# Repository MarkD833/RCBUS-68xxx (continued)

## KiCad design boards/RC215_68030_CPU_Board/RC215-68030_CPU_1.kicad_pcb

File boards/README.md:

# RCBUS-68000-Boards

These folders contain the KiCad (v8/v9/v10) design files for the various RCBus 68000 boards I'm currently testing.

## Series 1 boards

The series 1 boards are my first attempt at a 68000 based RCBus-80 system. Processor boards support autovectored interrupts only.

**NOTE:** The series 1 boards have been largly superseeded by the series 2 boards as my knowledge expanded and have generally been superseeded by the RC2xx series 2 boards.

| ID | Description | Notes |
| :---- | :---- | :---- |
| RC101 | 68000 processor card using the PLCC package variant of the 68000 | Use RC201 for vectored interrupt support |
| RC102 | 128K ROM & 1M RAM board | Use RC208 instead |
| RC103 | Dual MC68681 serial board - 4 serial ports | Use RC202 (2 serial ports only) for vectored interrupt support |
| RC104 | Dual MC68230 parallel interface / timer board | Use RC203 for vectored interrupt support (timer only) |
| RC105 | Dual MC68901 multifunction peripheral board | |
| RC106 | 68302 processor card using the PGA package | |
| RC107 | 1M ROM & 1M RAM board | Use RC208 instead |
| RC108 | 6 channel SPI master board - 3V3 and 5V ports | |
| RC109 | Serial / parallel / timer board | |
| RC110 | 68020 processor card using the PGA package | Use RC205 for vectored interrupt support |
| RC111 | SCC68692 DUART + MC68881 maths coprocessor | |

Note that the 68020 board is still very much at the prototype stage.

## Series 2 boards

The series 2 boards are based on my time spent with the series 1 boards and the hope is that the processor boards will feature a mixture of vectored and autovectored interrupts.

| ID | Description | Notes |
| :---- | :---- | :---- |
| RC200 | RCBus-80 Developers Backplane | |
| RC201 | 68000 PLCC processor board | Supports vectored interrupts |
| RC202 | SCC68692 DUART board | Bit banged SPI & I2C ports |
| RC203 | Dual MC68230 parallel interface / timer board | |
| RC204 | 1M ROM & 3M RAM board | Untested but likely replaced with RC209 shortly |
| RC205 | 68020 PGA processor board | Supports vectored interrupts |
| RC206 | 68008 PLCC processor board | |
| RC207 | 1M ROM & 1M RAM board - manual BOOT ROM switching | Abandoned - use RC208 instead |
| RC208 | 1M ROM & 1M RAM board - automatic BOOT ROM switching | |
| RC209 | 1M ROM & 3M RAM board - automatic BOOT ROM switching | |
| RC215 | 68EC030 PGA processor board | Supports vectored interrupts |
| RC216 | SCC68692 DUART + MC68882 Maths coprocessor | Bit banged I2C port |

Several of the series 2 boards are now working and I've put details in their respectove folders whilst others are still very much at the prototype stage.

## Notes
Make sure to look at the readme files in each board folder as they will detail any errors and corrections I've noticed so far as well as any thoughts on future enhancements etc.

A minimal series 2 system using a 68000, 68010, 68020 or 68EC030 processor requires an RC208 ROM/RAM board and a series 2 serial I/O board.

A minimal 68302 system would comprise of a 68302 CPU board and a ROM/RAM board.

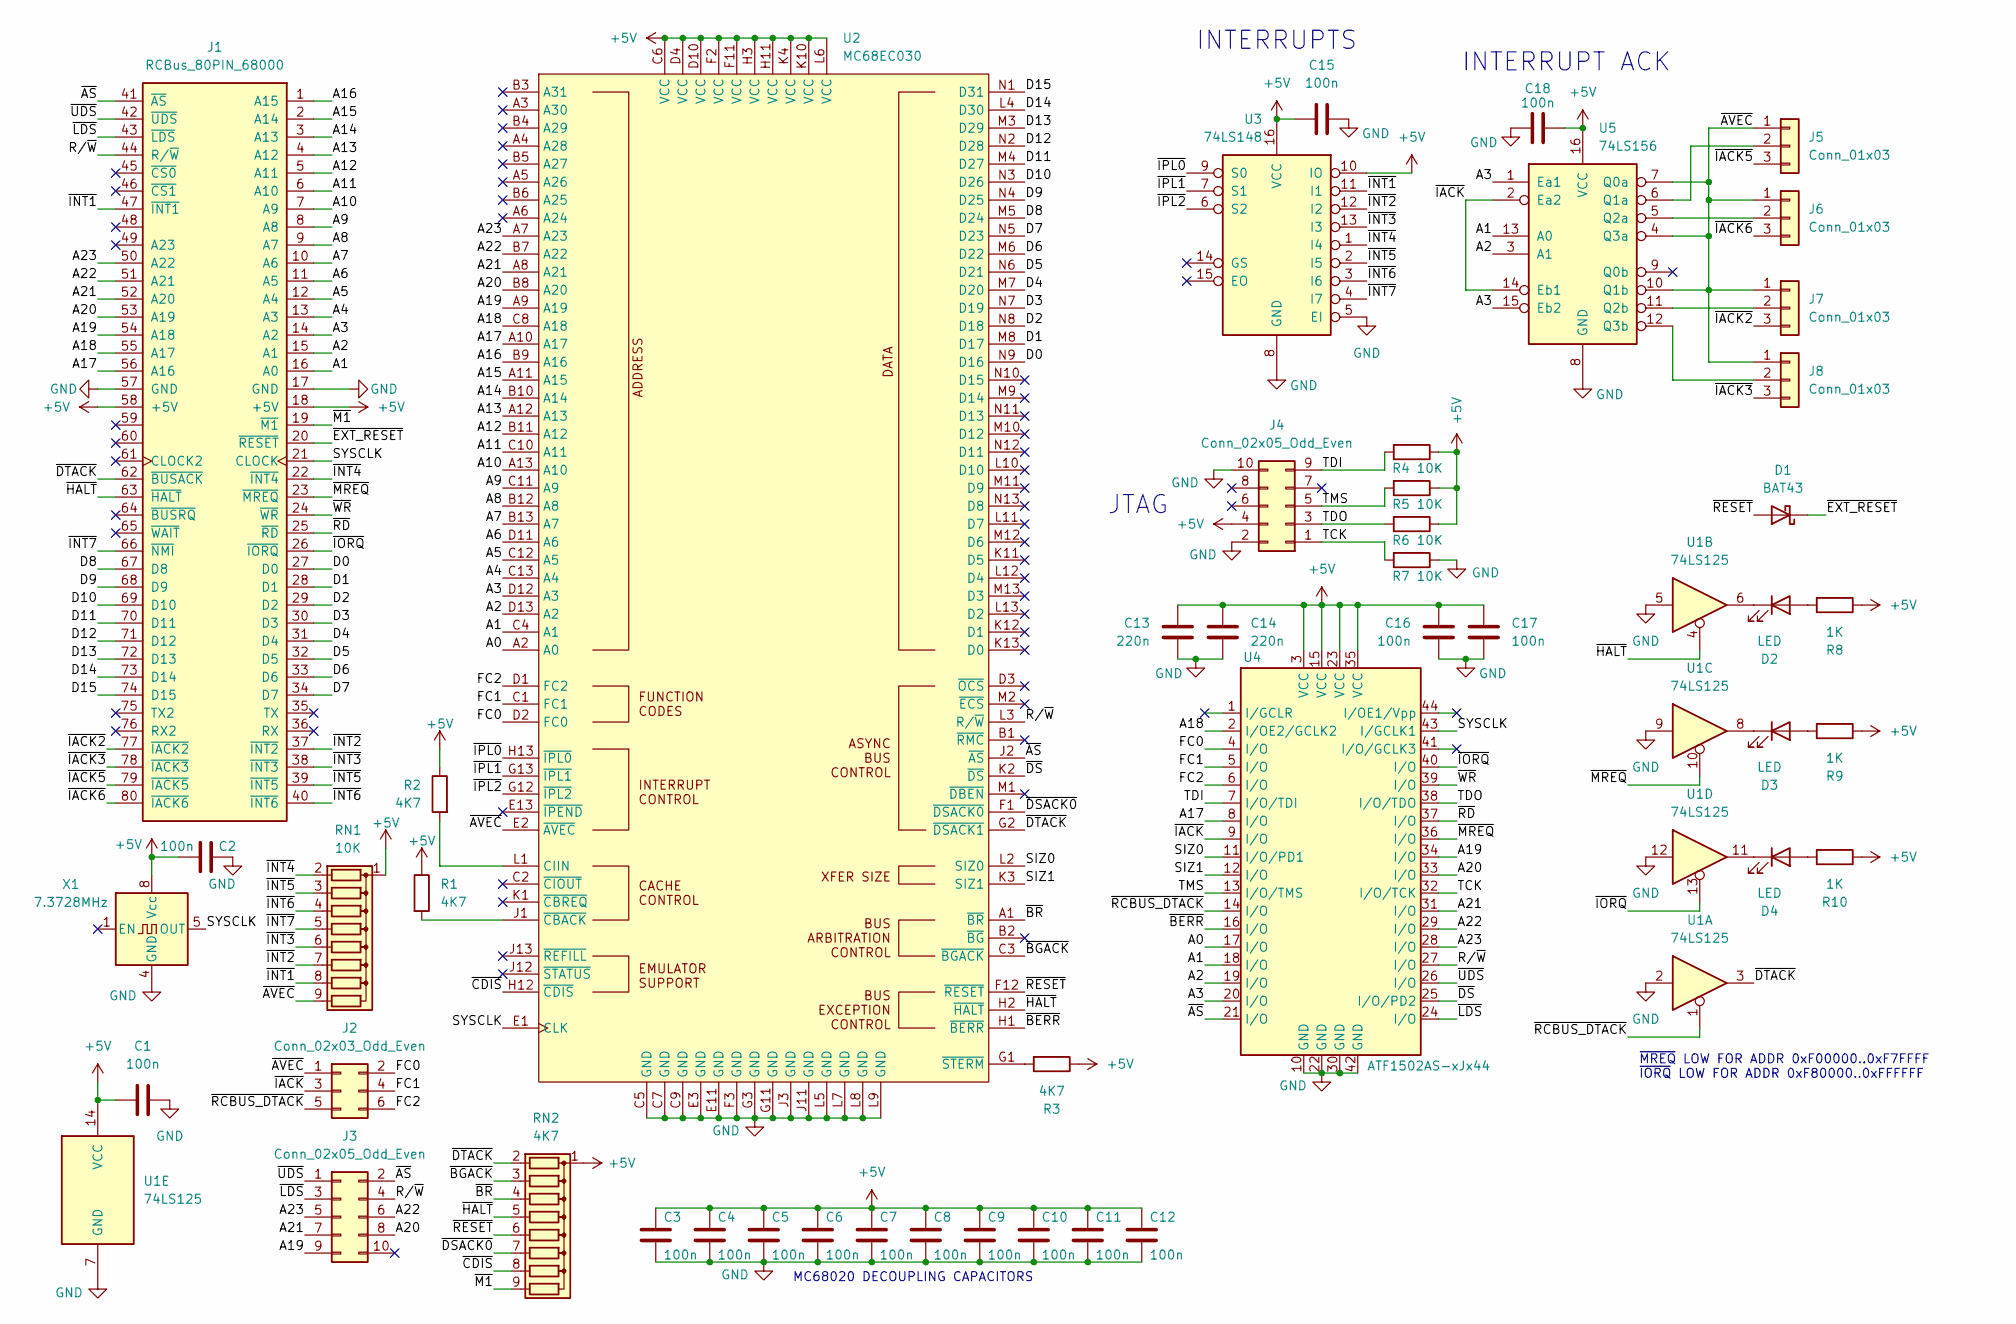
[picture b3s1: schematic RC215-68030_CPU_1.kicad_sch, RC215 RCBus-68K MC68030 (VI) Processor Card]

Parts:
C1, C2, C3, C4, C5, C6, C7, C8, C9, C10, C11, C12, C15, C16, C17, C18: 100n; C_0805_2012Metric_Pad1.18x1.45mm_HandSolder
C13, C14: 220n; C_0805_2012Metric_Pad1.18x1.45mm_HandSolder
D1: BAT43; D_DO-35_SOD27_P7.62mm_Horizontal
D2, D3, D4: LED; KingBright_WP934_1_LED
J1: RCBus_80PIN_68000; RCBus_80p_Medium
J2: Conn_02x03_Odd_Even; PinHeader_2x03_P2.54mm_Vertical
J3, J4: Conn_02x05_Odd_Even; PinHeader_2x05_P2.54mm_Vertical
J5, J6, J7, J8: Conn_01x03; PinHeader_1x03_P2.54mm_Vertical
R1, R2, R3: 4K7; R_0805_2012Metric_Pad1.20x1.40mm_HandSolder
R4, R5, R6, R7: 10K; R_0805_2012Metric_Pad1.20x1.40mm_HandSolder
R8, R9, R10: 1K; R_0805_2012Metric_Pad1.20x1.40mm_HandSolder
RN1: 10K; R_Array_SIP9
RN2: 4K7; R_Array_SIP9
U1: 74LS125; DIP-14_W7.62mm
U2: MC68EC030; PGA124
U3: 74LS148; DIP-16_W7.62mm
U4: ATF1502AS-xJx44; PLCC-44_THT-Socket
U5: 74LS156; DIP-16_W7.62mm
X1: 7.3728MHz; Oscillator_DIP-8

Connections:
+5V: C1.1, C2.2, C3.2, C4.2, C5.2, C6.2, C7.2, C8.2, C9.2, C10.2, C11.2, C12.2, C13.2, C14.2, C15.1, C16.1, C17.2, C18.1, J1.18 (+5V), J1.58 (+5V), J4.4, R1.1, R2.1, R3.1, R4.1, R5.1, R6.1, R8.1, R9.1, R10.1, RN1.1 (common), RN2.1 (common), U1.14 (VCC), U2.C6 (VCC), U2.D4 (VCC), U2.D10 (VCC), U2.F2 (VCC), U2.F11 (VCC), U2.H3 (VCC), U2.H11 (VCC), U2.K4 (VCC), U2.K10 (VCC), U2.L6 (VCC), U3.10 (IO), U3.16 (VCC), U4.3 (VCC), U4.15 (VCC), U4.23 (VCC), U4.35 (VCC), U5.16 (VCC), X1.8 (Vcc)
/A0: U2.A2 (A0), U4.17 (I/O)
/A1: J1.16 (A0), U2.C4 (A1), U4.18 (I/O), U5.13 (A0)
/A2: J1.15 (A1), U2.D13 (A2), U4.19 (I/O), U5.3 (A1)
/A3: J1.14 (A2), U2.D12 (A3), U4.20 (I/O), U5.1 (Ea1), U5.15 (Eb2)
/A4: J1.13 (A3), U2.C13 (A4)
/A5: J1.12 (A4), U2.C12 (A5)
/A6: J1.11 (A5), U2.D11 (A6)
/A7: J1.10 (A6), U2.B13 (A7)
/A8: J1.9 (A7), U2.B12 (A8)
/A9: J1.8 (A8), U2.C11 (A9)
/A10: J1.7 (A9), U2.A13 (A10)
/A11: J1.6 (A10), U2.C10 (A11)
/A12: J1.5 (A11), U2.B11 (A12)
/A13: J1.4 (A12), U2.A12 (A13)
/A14: J1.3 (A13), U2.B10 (A14)
/A15: J1.2 (A14), U2.A11 (A15)
/A16: J1.1 (A15), U2.B9 (A16)
/A17: J1.56 (A16), U2.A10 (A17), U4.8 (I/O)
/A18: J1.55 (A17), U2.C8 (A18), U4.2 (I/OE2/GCLK2)
/A19: J1.54 (A18), J3.9, U2.A9 (A19), U4.34 (I/O)
/A20: J1.53 (A19), J3.8, U2.B8 (A20), U4.33 (I/O)
/A21: J1.52 (A20), J3.7, U2.A8 (A21), U4.31 (I/O)
/A22: J1.51 (A21), J3.6, U2.B7 (A22), U4.29 (I/O)
/A23: J1.50 (A22), J3.5, U2.A7 (A23), U4.28 (I/O)
/D0: J1.27 (D0), U2.N9 (D16)
/D1: J1.28 (D1), U2.M8 (D17)
/D2: J1.29 (D2), U2.N8 (D18)
/D3: J1.30 (D3), U2.N7 (D19)
/D4: J1.31 (D4), U2.M7 (D20)
/D5: J1.32 (D5), U2.N6 (D21)
/D6: J1.33 (D6), U2.M6 (D22)
/D7: J1.34 (D7), U2.N5 (D23)
/D8: J1.67 (D8), U2.M5 (D24)
/D9: J1.68 (D9), U2.N4 (D25)
/D10: J1.69 (D10), U2.N3 (D26)
/D11: J1.70 (D11), U2.M4 (D27)
/D12: J1.71 (D12), U2.N2 (D28)
/D13: J1.72 (D13), U2.M3 (D29)
/D14: J1.73 (D14), U2.L4 (D30)
/D15: J1.74 (D15), U2.N1 (D31)
/FC0: J2.2, U2.D2 (FC0), U4.4 (I/O)
/FC1: J2.4, U2.C1 (FC1), U4.5 (I/O)
/FC2: J2.6, U2.D1 (FC2), U4.6 (I/O)
/R/~W: J1.44 (R/~W), J3.4, U2.L3 (R/~W), U4.27 (I/O)
/SIZ0: U2.L2 (SIZ0), U4.11 (I/O/PD1)
/SIZ1: U2.K3 (SIZ1), U4.12 (I/O)
/SYSCLK: J1.21 (CLOCK), U2.E1 (CLK), U4.43 (I/GCLK1), X1.5 (OUT)
/TCK: J4.1, R7.2, U4.32 (I/O/TCK)
/TDI: J4.9, R4.2, U4.7 (I/O/TDI)
/TDO: J4.3, R6.2, U4.38 (I/O/TDO)
/TMS: J4.5, R5.2, U4.13 (I/O/TMS)
/~AS: J1.41 (~AS), J3.2, U2.J2 (~AS), U4.21 (I/O)
/~AVEC: J2.1, J5.1, J6.1, J7.1, J8.1, RN1.9 (R8), U2.E2 (~AVEC), U5.4 (Q3a), U5.7 (Q0a), U5.10 (Q1b)
/~BERR: U2.H1 (~BERR), U4.16 (I/O)
/~BGACK: RN2.3 (R2), U2.C3 (~BGACK)
/~BR: RN2.4 (R3), U2.A1 (~BR)
/~CDIS: RN2.8 (R7), U2.H12 (~CDIS)
/~DSACK0: RN2.7 (R6), U2.F1 (~DSACK0)
/~DS: U2.K2 (~DS), U4.25 (I/O/PD2)
/~DTACK: J1.62 (~BUSACK), RN2.2 (R1), U1.3, U2.G2 (~DSACK1)
/~EXT_RESET: D1.1 (K), J1.20 (~RESET)
/~HALT: J1.63 (~HALT), RN2.5 (R4), U1.4, U2.H2 (~HALT)
/~IACK2: J1.77 (~IACK2), J7.3
/~IACK3: J1.78 (~IACK3), J8.3
/~IACK5: J1.79 (~IACK5), J5.3
/~IACK6: J1.80 (~IACK6), J6.3
/~IACK: J2.3, U4.9 (I/O), U5.2 (Ea2), U5.14 (Eb1)
/~INT1: J1.47 (~INT1), RN1.8 (R7), U3.11 (I1)
/~INT2: J1.37 (~INT2), RN1.7 (R6), U3.12 (I2)
/~INT3: J1.38 (~INT3), RN1.6 (R5), U3.13 (I3)
/~INT4: J1.22 (~INT4), RN1.2 (R1), U3.1 (I4)
/~INT5: J1.39 (~INT5), RN1.3 (R2), U3.2 (I5)
/~INT6: J1.40 (~INT6), RN1.4 (R3), U3.3 (I6)
/~INT7: J1.66 (~NMI), RN1.5 (R4), U3.4 (I7)
/~IORQ: J1.26 (~IORQ), U1.13, U4.40 (I/O)
/~IPL0: U2.H13 (~IPL0), U3.9 (S0)
/~IPL1: U2.G13 (~IPL1), U3.7 (S1)
/~IPL2: U2.G12 (~IPL2), U3.6 (S2)
/~LDS: J1.43 (~LDS), J3.3, U4.24 (I/O)
/~M1: J1.19 (~M1), RN2.9 (R8)
/~MREQ: J1.23 (~MREQ), U1.10, U4.36 (I/O)
/~RCBUS_DTACK: J2.5, U1.1, U4.14 (I/O)
/~RD: J1.25 (~RD), U4.37 (I/O)
/~RESET: D1.2 (A), RN2.6 (R5), U2.F12 (~RESET)
/~UDS: J1.42 (~UDS), J3.1, U4.26 (I/O)
/~WR: J1.24 (~WR), U4.39 (I/O)
GND: C1.2, C2.1, C3.1, C4.1, C5.1, C6.1, C7.1, C8.1, C9.1, C10.1, C11.1, C12.1, C13.1, C14.1, C15.2, C16.2, C17.1, C18.2, J1.17 (GND), J1.57 (GND), J4.2, J4.10, R7.1, U1.2, U1.5, U1.7 (GND), U1.9, U1.12, U2.C5 (GND), U2.C7 (GND), U2.C9 (GND), U2.E3 (GND), U2.E11 (GND), U2.F3 (GND), U2.G3 (GND), U2.G11 (GND), U2.J3 (GND), U2.J11 (GND), U2.L5 (GND), U2.L7 (GND), U2.L8 (GND), U2.L9 (GND), U3.5 (EI), U3.8 (GND), U4.10 (GND), U4.22 (GND), U4.30 (GND), U4.42 (GND), U5.8 (GND), X1.4 (GND)
unnamed: D2.2 (A), R8.2
unnamed: D2.1 (K), U1.6
unnamed: D3.2 (A), R9.2
unnamed: D3.1 (K), U1.8
unnamed: D4.2 (A), R10.2
unnamed: D4.1 (K), U1.11
unnamed: J5.2, U5.6 (Q1a)
unnamed: J6.2, U5.5 (Q2a)
unnamed: J7.2, U5.11 (Q2b)
unnamed: J8.2, U5.12 (Q3b)
unnamed: R2.2, U2.L1 (CIIN)
unnamed: R1.2, U2.J1 (~CBACK)
unnamed: R3.2, U2.G1 (~STERM)

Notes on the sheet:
MC68020 DECOUPLING CAPACITORS
INTERRUPTS
~{MREQ} LOW FOR ADDR 0xF00000..0xF7FFFF ~{IORQ} LOW FOR ADDR 0xF80000..0xFFFFFF
INTERRUPT ACK
JTAG

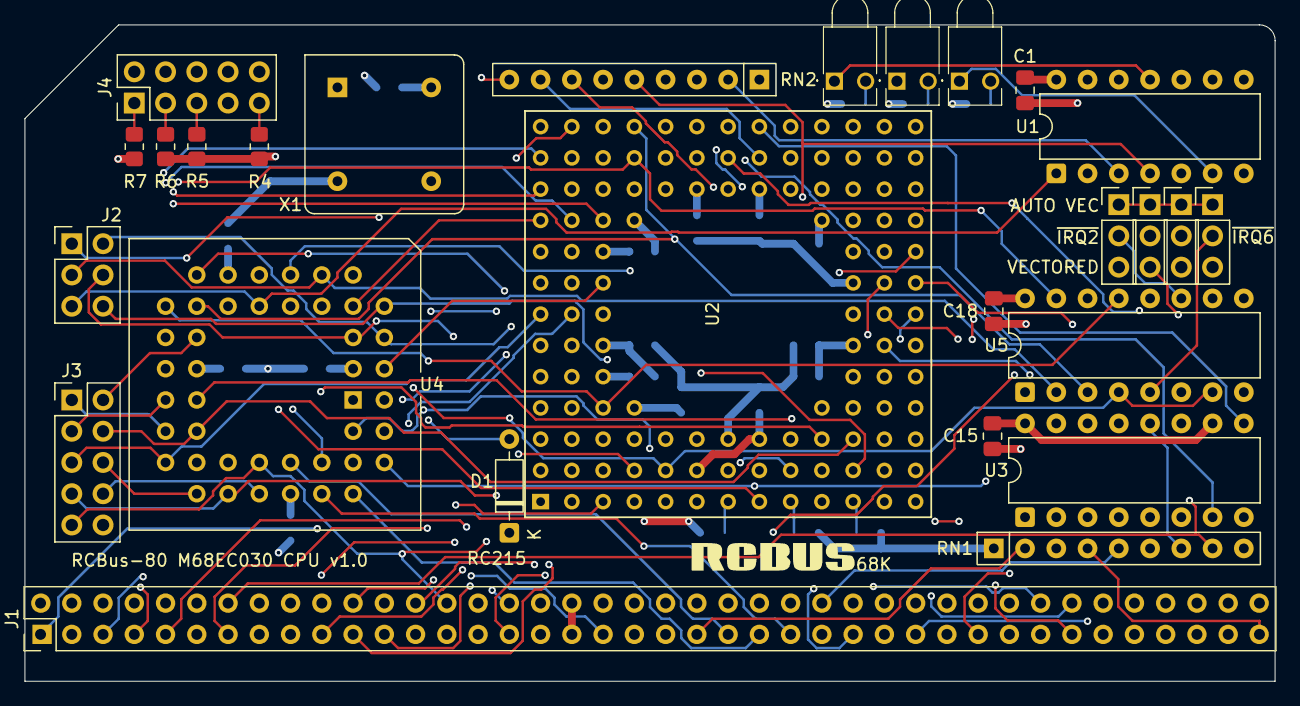
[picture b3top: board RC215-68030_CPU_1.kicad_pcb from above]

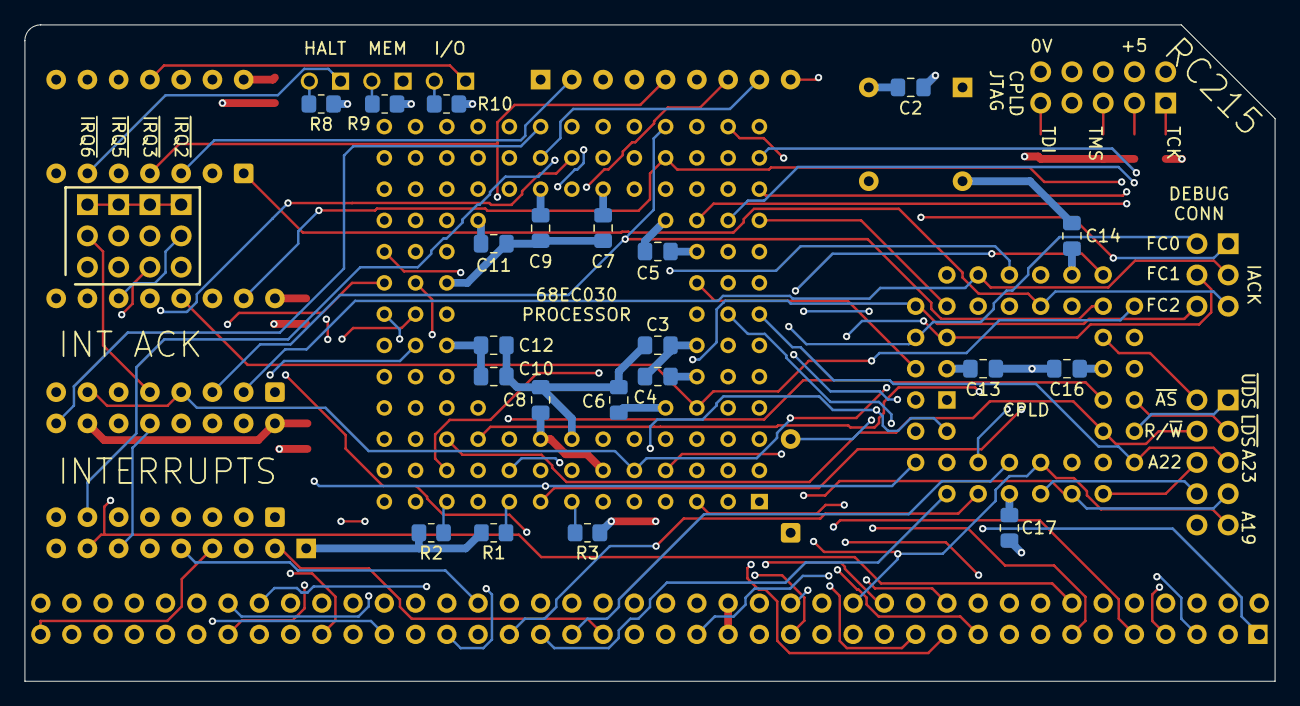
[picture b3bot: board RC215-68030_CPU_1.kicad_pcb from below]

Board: 4 copper layers, 101.6 x 53.3 mm, 48 parts (21 on the bottom side), 101 nets.

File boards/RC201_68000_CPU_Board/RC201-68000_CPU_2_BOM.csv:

"Reference","Value","Footprint","Qty","Description"
"C1,C2,C3,C5,C6,C7,C8,C9,C10,C11,C12","100n","Capacitor_THT:C_Disc_D5.0mm_W2.5mm_P2.50mm","11","Unpolarized ceramic capacitor"
"D1,D2,D5","BAT43","Diode_THT:D_DO-35_SOD27_P7.62mm_Horizontal","3","30V 0.2A Small Signal Schottky Diode, DO-35"
"D3,D4","LED","LED_THT:LED_D3.0mm","2","Light emitting diode"
"J1","Conn_02x04_Odd_Even","Connector_PinHeader_2.54mm:PinHeader_2x04_P2.54mm_Vertical","1","Generic connector, double row, 02x04"
"J2","RCBus_80PIN_68000","MyLibrary2023:RCBus_80p_Medium","1","Generic connector, double row, 02x40, right angle"
"J3,J5,J6,J7","Conn_01x03","Connector_PinHeader_2.54mm:PinHeader_1x03_P2.54mm_Vertical","4","Generic connector, single row, 01x03, script generated (kicad-library-utils/schlib/autogen/connector/)"
"J4","Conn_01x02","Connector_PinHeader_2.54mm:PinHeader_1x02_P2.54mm_Vertical","1","Generic connector, single row, 01x02"
"R1,R2","1K","Resistor_THT:R_Axial_DIN0207_L6.3mm_D2.5mm_P7.62mm_Horizontal","2","Resistor"
"RN1","4K7","Resistor_THT:R_Array_SIP9","1","8 resistor network, star topology, bussed resistors, small symbol"
"RN2","10K","Resistor_THT:R_Array_SIP9","1","8 resistor network, star topology, bussed resistors, small symbol"
"U1","","Package_LCC:PLCC-68_THT-Socket","1",""
"U2","74LS04","MyLibrary2023:DIP-14_W7.62mm","1","Hex Inverter"
"U3","74LS148","MyLibrary2023:DIP-16_W7.62mm","1","8 line to 3 line priority encoder"
"U4","74LS20","MyLibrary2023:DIP-14_W7.62mm","1","Dual 4-input NAND"
"U5","74LS139","MyLibrary2023:DIP-16_W7.62mm","1","Dual Decoder 1 of 4, Active low outputs"
"U6,U8","74LS175","MyLibrary2023:DIP-16_W7.62mm","2","4-bit D Flip-Flop, reset"
"U7","74LS156","MyLibrary2023:DIP-16_W7.62mm","1","Dual 2 to 4 lines Decoder/Demultiplexer, Open Collector"
"U9","74LS00","MyLibrary2023:DIP-14_W7.62mm","1","quad 2-input NAND gate"
"X1","7.3728MHz","Oscillator:Oscillator_DIP-8","1","Crystal Clock Oscillator, DIP8-style metal package"

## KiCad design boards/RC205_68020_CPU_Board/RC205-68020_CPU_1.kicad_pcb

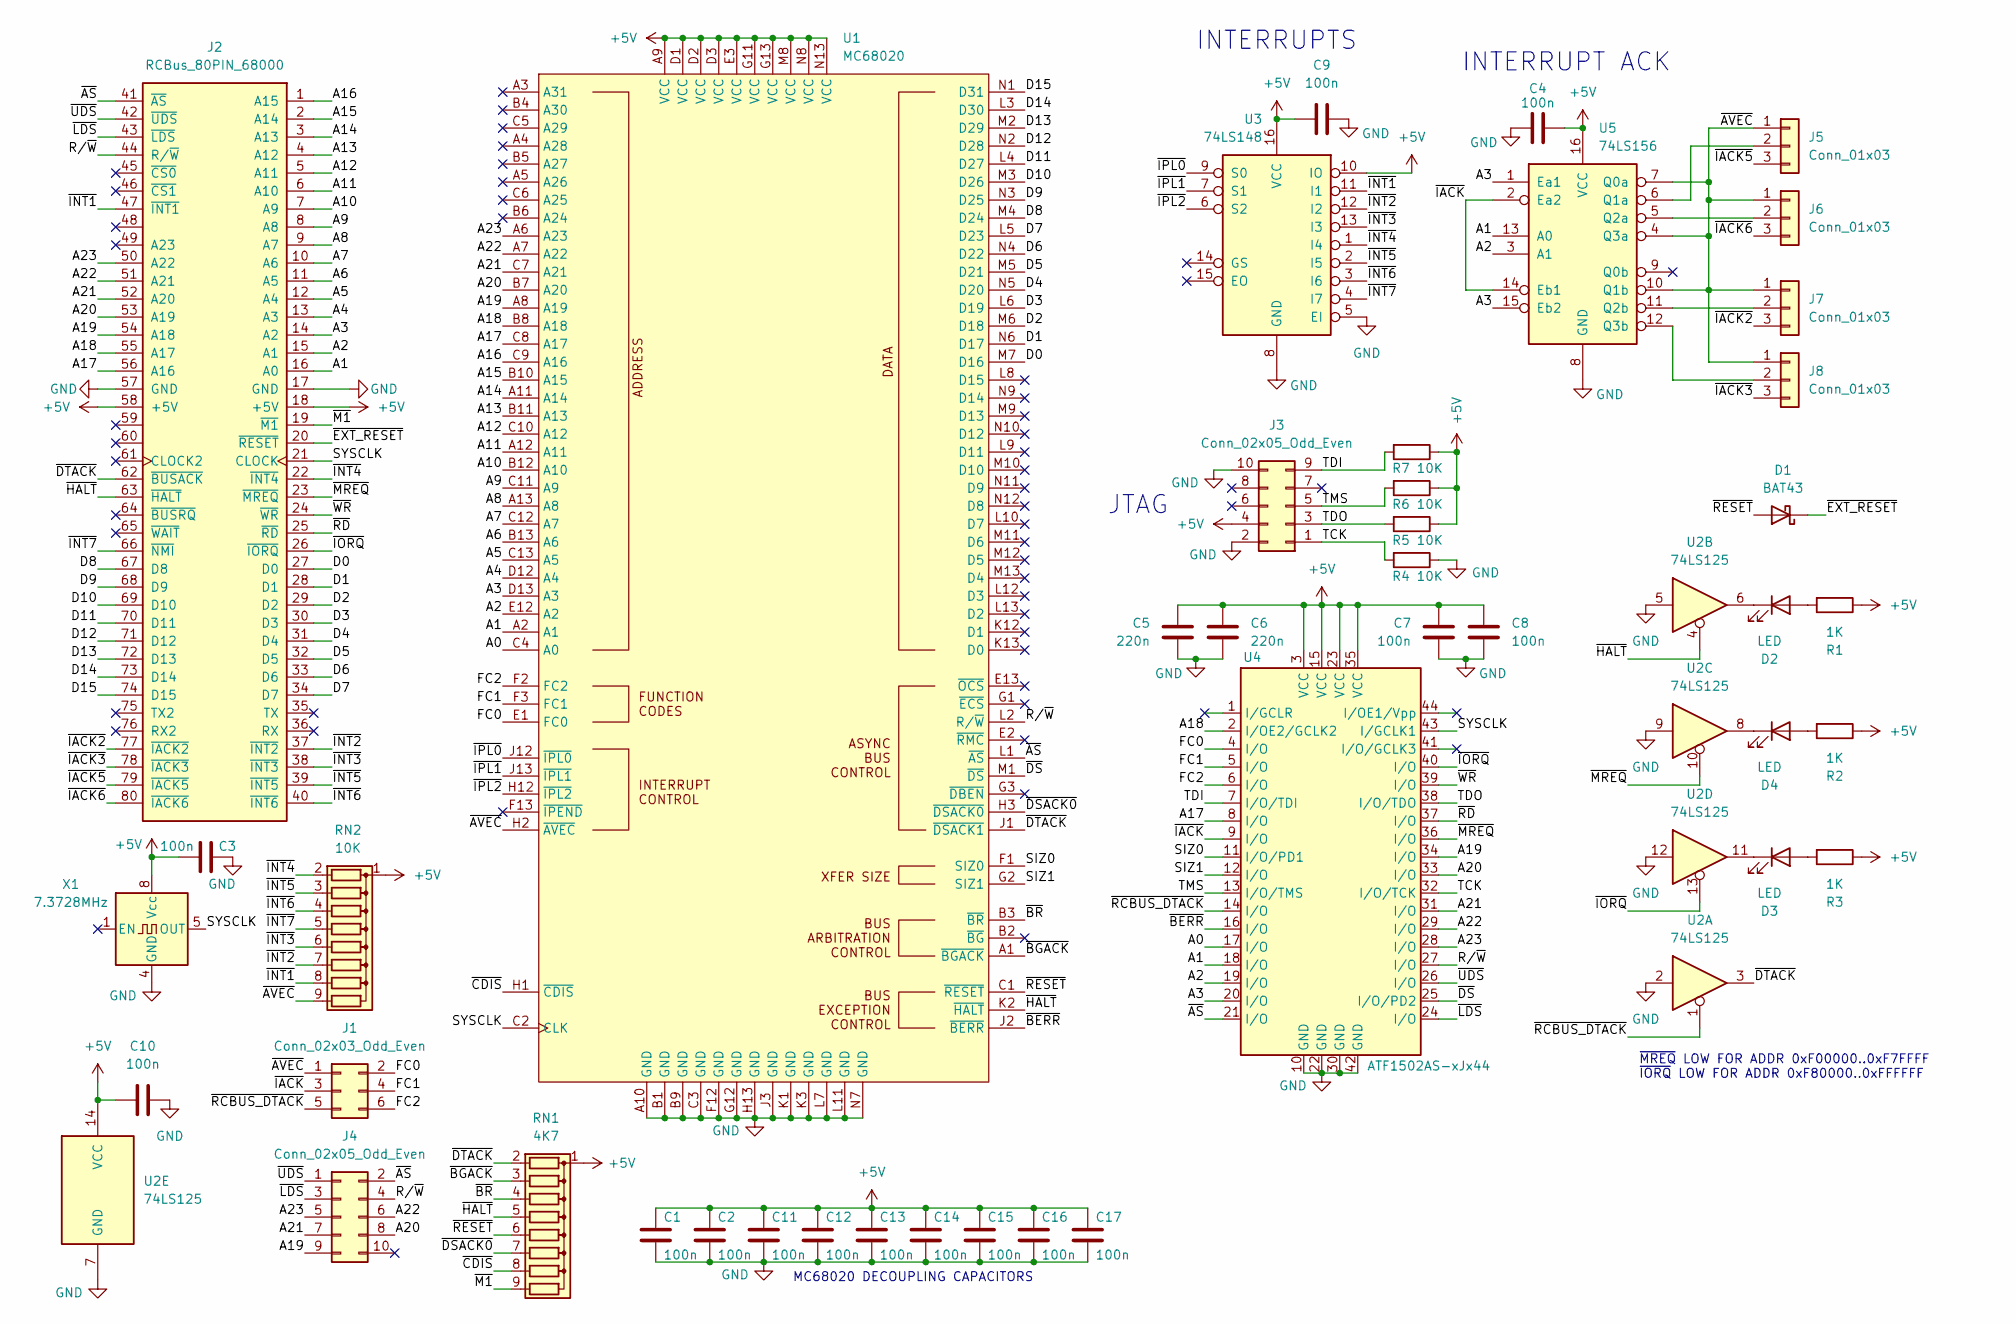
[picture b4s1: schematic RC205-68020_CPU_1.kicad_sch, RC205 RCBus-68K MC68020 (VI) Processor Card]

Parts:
C1, C2, C3, C4, C7, C8, C9, C10, C11, C12, C13, C14, C15, C16, C17: 100n; C_0805_2012Metric_Pad1.18x1.45mm_HandSolder
C5, C6: 220n; C_0805_2012Metric_Pad1.18x1.45mm_HandSolder
D1: BAT43; D_DO-35_SOD27_P7.62mm_Horizontal
D2, D3, D4: LED; LED_D3.0mm
J1: Conn_02x03_Odd_Even; PinHeader_2x03_P2.54mm_Vertical
J2: RCBus_80PIN_68000; RCBus_80p_Medium
J3, J4: Conn_02x05_Odd_Even; PinHeader_2x05_P2.54mm_Vertical
J5, J6, J7, J8: Conn_01x03; PinHeader_1x03_P2.54mm_Vertical
R1, R2, R3: 1K; R_0805_2012Metric_Pad1.20x1.40mm_HandSolder
R4, R5, R6, R7: 10K; R_0805_2012Metric_Pad1.20x1.40mm_HandSolder
RN1: 4K7; R_Array_SIP9
RN2: 10K; R_Array_SIP9
U1: MC68020; PGA114
U2: 74LS125; DIP-14_W7.62mm
U3: 74LS148; DIP-16_W7.62mm
U4: ATF1502AS-xJx44; PLCC-44_THT-Socket
U5: 74LS156; DIP-16_W7.62mm
X1: 7.3728MHz; Oscillator_DIP-8

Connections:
+5V: C1.2, C2.2, C3.2, C4.1, C5.2, C6.2, C7.1, C8.2, C9.1, C10.1, C11.2, C12.2, C13.2, C14.2, C15.2, C16.2, C17.2, J2.18 (+5V), J2.58 (+5V), J3.4, R1.1, R2.1, R3.1, R5.1, R6.1, R7.1, RN1.1 (common), RN2.1 (common), U1.A9 (VCC), U1.D1 (VCC), U1.D2 (VCC), U1.D3 (VCC), U1.E3 (VCC), U1.G11 (VCC), U1.G13 (VCC), U1.M8 (VCC), U1.N8 (VCC), U1.N13 (VCC), U2.14 (VCC), U3.10 (IO), U3.16 (VCC), U4.3 (VCC), U4.15 (VCC), U4.23 (VCC), U4.35 (VCC), U5.16 (VCC), X1.8 (Vcc)
/A0: U1.C4 (A0), U4.17 (I/O)
/A1: J2.16 (A0), U1.A2 (A1), U4.18 (I/O), U5.13 (A0)
/A2: J2.15 (A1), U1.E12 (A2), U4.19 (I/O), U5.3 (A1)
/A3: J2.14 (A2), U1.D13 (A3), U4.20 (I/O), U5.1 (Ea1), U5.15 (Eb2)
/A4: J2.13 (A3), U1.D12 (A4)
/A5: J2.12 (A4), U1.C13 (A5)
/A6: J2.11 (A5), U1.B13 (A6)
/A7: J2.10 (A6), U1.C12 (A7)
/A8: J2.9 (A7), U1.A13 (A8)
/A9: J2.8 (A8), U1.C11 (A9)
/A10: J2.7 (A9), U1.B12 (A10)
/A11: J2.6 (A10), U1.A12 (A11)
/A12: J2.5 (A11), U1.C10 (A12)
/A13: J2.4 (A12), U1.B11 (A13)
/A14: J2.3 (A13), U1.A11 (A14)
/A15: J2.2 (A14), U1.B10 (A15)
/A16: J2.1 (A15), U1.C9 (A16)
/A17: J2.56 (A16), U1.C8 (A17), U4.8 (I/O)
/A18: J2.55 (A17), U1.B8 (A18), U4.2 (I/OE2/GCLK2)
/A19: J2.54 (A18), J4.9, U1.A8 (A19), U4.34 (I/O)
/A20: J2.53 (A19), J4.8, U1.B7 (A20), U4.33 (I/O)
/A21: J2.52 (A20), J4.7, U1.C7 (A21), U4.31 (I/O)
/A22: J2.51 (A21), J4.6, U1.A7 (A22), U4.29 (I/O)
/A23: J2.50 (A22), J4.5, U1.A6 (A23), U4.28 (I/O)
/D0: J2.27 (D0), U1.M7 (D16)
/D1: J2.28 (D1), U1.N6 (D17)
/D2: J2.29 (D2), U1.M6 (D18)
/D3: J2.30 (D3), U1.L6 (D19)
/D4: J2.31 (D4), U1.N5 (D20)
/D5: J2.32 (D5), U1.M5 (D21)
/D6: J2.33 (D6), U1.N4 (D22)
/D7: J2.34 (D7), U1.L5 (D23)
/D8: J2.67 (D8), U1.M4 (D24)
/D9: J2.68 (D9), U1.N3 (D25)
/D10: J2.69 (D10), U1.M3 (D26)
/D11: J2.70 (D11), U1.L4 (D27)
/D12: J2.71 (D12), U1.N2 (D28)
/D13: J2.72 (D13), U1.M2 (D29)
/D14: J2.73 (D14), U1.L3 (D30)
/D15: J2.74 (D15), U1.N1 (D31)
/FC0: J1.2, U1.E1 (FC0), U4.4 (I/O)
/FC1: J1.4, U1.F3 (FC1), U4.5 (I/O)
/FC2: J1.6, U1.F2 (FC2), U4.6 (I/O)
/R/~W: J2.44 (R/~W), J4.4, U1.L2 (R/~W), U4.27 (I/O)
/SIZ0: U1.F1 (SIZ0), U4.11 (I/O/PD1)
/SIZ1: U1.G2 (SIZ1), U4.12 (I/O)
/SYSCLK: J2.21 (CLOCK), U1.C2 (CLK), U4.43 (I/GCLK1), X1.5 (OUT)
/TCK: J3.1, R4.2, U4.32 (I/O/TCK)
/TDI: J3.9, R7.2, U4.7 (I/O/TDI)
/TDO: J3.3, R5.2, U4.38 (I/O/TDO)
/TMS: J3.5, R6.2, U4.13 (I/O/TMS)
/~AS: J2.41 (~AS), J4.2, U1.L1 (~AS), U4.21 (I/O)
/~AVEC: J1.1, J5.1, J6.1, J7.1, J8.1, RN2.9 (R8), U1.H2 (~AVEC), U5.4 (Q3a), U5.7 (Q0a), U5.10 (Q1b)
/~BERR: U1.J2 (~BERR), U4.16 (I/O)
/~BGACK: RN1.3 (R2), U1.A1 (~BGACK)
/~BR: RN1.4 (R3), U1.B3 (~BR)
/~CDIS: RN1.8 (R7), U1.H1 (~CDIS)
/~DSACK0: RN1.7 (R6), U1.H3 (~DSACK0)
/~DS: U1.M1 (~DS), U4.25 (I/O/PD2)
/~DTACK: J2.62 (~BUSACK), RN1.2 (R1), U1.J1 (~DSACK1), U2.3
/~EXT_RESET: D1.1 (K), J2.20 (~RESET)
/~HALT: J2.63 (~HALT), RN1.5 (R4), U1.K2 (~HALT), U2.4
/~IACK2: J2.77 (~IACK2), J7.3
/~IACK3: J2.78 (~IACK3), J8.3
/~IACK5: J2.79 (~IACK5), J5.3
/~IACK6: J2.80 (~IACK6), J6.3
/~IACK: J1.3, U4.9 (I/O), U5.2 (Ea2), U5.14 (Eb1)
/~INT1: J2.47 (~INT1), RN2.8 (R7), U3.11 (I1)
/~INT2: J2.37 (~INT2), RN2.7 (R6), U3.12 (I2)
/~INT3: J2.38 (~INT3), RN2.6 (R5), U3.13 (I3)
/~INT4: J2.22 (~INT4), RN2.2 (R1), U3.1 (I4)
/~INT5: J2.39 (~INT5), RN2.3 (R2), U3.2 (I5)
/~INT6: J2.40 (~INT6), RN2.4 (R3), U3.3 (I6)
/~INT7: J2.66 (~NMI), RN2.5 (R4), U3.4 (I7)
/~IORQ: J2.26 (~IORQ), U2.13, U4.40 (I/O)
/~IPL0: U1.J12 (~IPL0), U3.9 (S0)
/~IPL1: U1.J13 (~IPL1), U3.7 (S1)
/~IPL2: U1.H12 (~IPL2), U3.6 (S2)
/~LDS: J2.43 (~LDS), J4.3, U4.24 (I/O)
/~M1: J2.19 (~M1), RN1.9 (R8)
/~MREQ: J2.23 (~MREQ), U2.10, U4.36 (I/O)
/~RCBUS_DTACK: J1.5, U2.1, U4.14 (I/O)
/~RD: J2.25 (~RD), U4.37 (I/O)
/~RESET: D1.2 (A), RN1.6 (R5), U1.C1 (~RESET)
/~UDS: J2.42 (~UDS), J4.1, U4.26 (I/O)
/~WR: J2.24 (~WR), U4.39 (I/O)
GND: C1.1, C2.1, C3.1, C4.2, C5.1, C6.1, C7.2, C8.1, C9.2, C10.2, C11.1, C12.1, C13.1, C14.1, C15.1, C16.1, C17.1, J2.17 (GND), J2.57 (GND), J3.2, J3.10, R4.1, U1.A10 (GND), U1.B1 (GND), U1.B9 (GND), U1.C3 (GND), U1.F12 (GND), U1.G12 (GND), U1.H13 (GND), U1.J3 (GND), U1.K1 (GND), U1.K3 (GND), U1.L7 (GND), U1.L11 (GND), U1.N7 (GND), U2.2, U2.5, U2.7 (GND), U2.9, U2.12, U3.5 (EI), U3.8 (GND), U4.10 (GND), U4.22 (GND), U4.30 (GND), U4.42 (GND), U5.8 (GND), X1.4 (GND)
unnamed: D2.2 (A), R1.2
unnamed: D2.1 (K), U2.6
unnamed: D3.2 (A), R3.2
unnamed: D3.1 (K), U2.11
unnamed: D4.2 (A), R2.2
unnamed: D4.1 (K), U2.8
unnamed: J5.2, U5.6 (Q1a)
unnamed: J6.2, U5.5 (Q2a)
unnamed: J7.2, U5.11 (Q2b)
unnamed: J8.2, U5.12 (Q3b)

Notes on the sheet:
MC68020 DECOUPLING CAPACITORS
INTERRUPTS
~{MREQ} LOW FOR ADDR 0xF00000..0xF7FFFF ~{IORQ} LOW FOR ADDR 0xF80000..0xFFFFFF
INTERRUPT ACK
JTAG

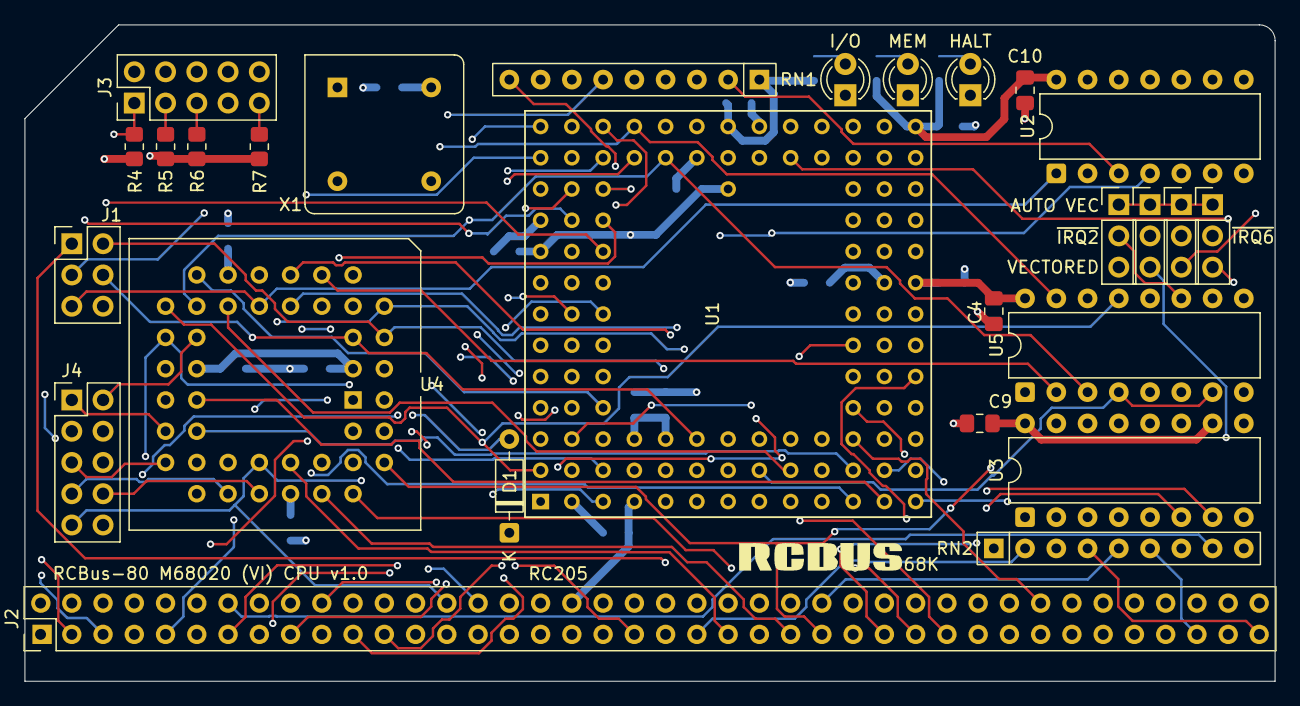
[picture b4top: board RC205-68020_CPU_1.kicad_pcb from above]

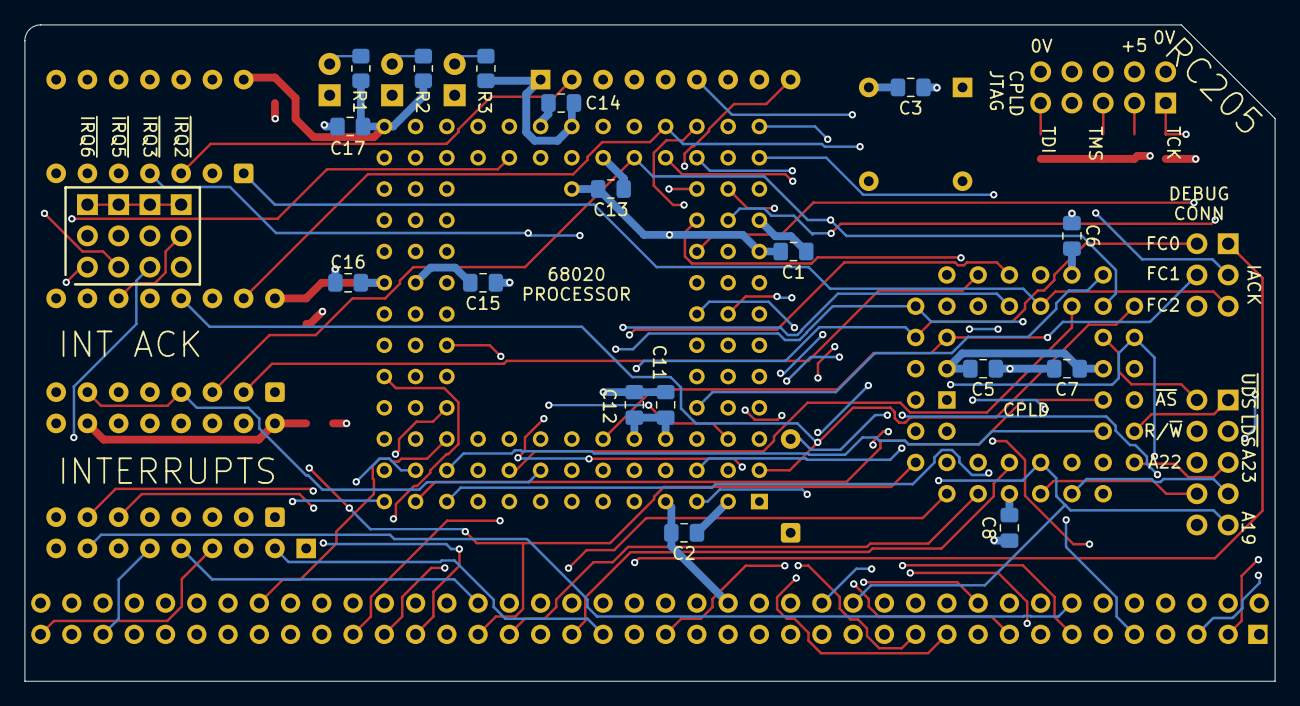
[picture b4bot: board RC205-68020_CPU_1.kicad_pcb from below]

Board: 4 copper layers, 101.6 x 53.3 mm, 44 parts (17 on the bottom side), 98 nets.

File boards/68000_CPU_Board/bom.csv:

Designator,Footprint,Quantity,Value,LCSC Part #
"C1, C10, C11, C2, C3, C5, C6, C7, C8, C9",C_Disc_D5.0mm_W2.5mm_P2.50mm,10,100n,
"D1, D2",D_DO-35_SOD27_P7.62mm_Horizontal,2,BAT43,
"D3, D4, D5",LED_D3.0mm,3,LED,
J1,PinHeader_2x04_P2.54mm_Vertical,1,Conn_02x04_Odd_Even,
J2,RCBus_80p_Medium,1,RCBus_80PIN_68000,
J4,PinHeader_1x02_P2.54mm_Vertical,1,Conn_01x02,
"R1, R2, R3",R_Axial_DIN0207_L6.3mm_D2.5mm_P7.62mm_Horizontal,3,1K,
RN1,R_Array_SIP9,1,4K7,
RN2,R_Array_SIP9,1,10K,
U1,PLCC-68_THT-Socket,1,MC68000FN,
U2,DIP-14_W7.62mm_Socket,1,74LS125,
U3,DIP-16_W7.62mm_Socket,1,74LS148,
U4,DIP-14_W7.62mm_Socket,1,74LS10,
U5,DIP-16_W7.62mm_Socket,1,74LS139,
"U6, U8",DIP-16_W7.62mm_Socket,2,74LS175,
U9,DIP-14_W7.62mm_Socket,1,74LS00,
X1,Oscillator_DIP-8,1,CXO_DIP8,
